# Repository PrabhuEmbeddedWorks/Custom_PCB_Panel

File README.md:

# Custom_PCB_Panel
Tools-KiCad

Designed a custom KiCad symbol and footprint for the DigiSpark PCB, ensuring accurate pin mappings, electrical properties, and mechanical details. The symbol was created with proper pin labeling, while the footprint included precise pad placements, silkscreen, and courtyard outlines for proper component placement and assembly. Both were saved and integrated into the schematic and layout for the DigiSpark project.

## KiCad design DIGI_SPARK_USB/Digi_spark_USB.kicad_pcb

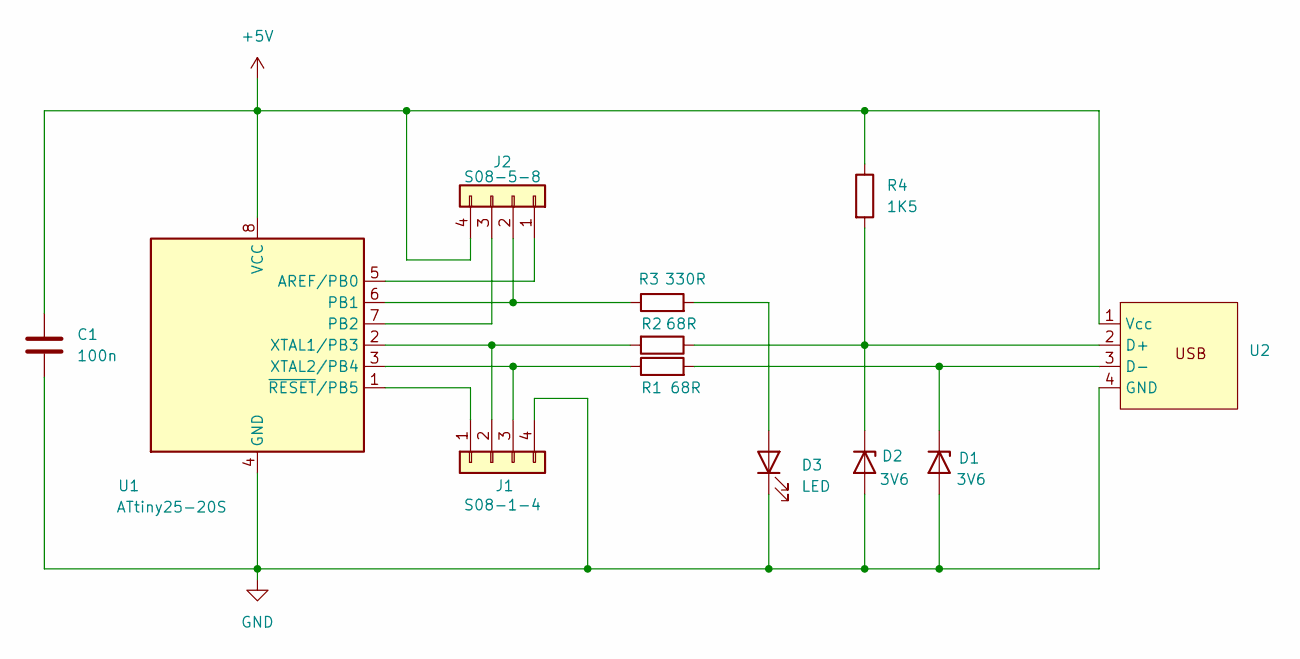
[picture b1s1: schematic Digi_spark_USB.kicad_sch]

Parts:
C1: 100n; C_1206_3216Metric_Pad1.33x1.80mm_HandSolder
D1, D2: 3V6; D_SOD-123
D3: LED; LED_Oval_W5.2mm_H3.8mm
J1: S08-1-4; SolderWire-0.5sqmm_1x04_P4.6mm_D0.9mm_OD2.1mm
J2: S08-5-8; SolderWire-0.5sqmm_1x04_P4.6mm_D0.9mm_OD2.1mm
R1, R2: 68R; R_0805_2012Metric_Pad1.20x1.40mm_HandSolder
R3: 330R; R_0805_2012Metric_Pad1.20x1.40mm_HandSolder
R4: 1K5; R_0805_2012Metric_Pad1.20x1.40mm_HandSolder
U1: ATtiny25-20S; SOIC-8W_5.3x5.3mm_P1.27mm
U2: PCB_USB_connector

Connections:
+5V: C1.1, J2.4, R4.1, U1.8 (VCC), U2.1 (GND)
GND: C1.2, D1.2 (A), D2.2 (A), D3.1 (K), J1.4, U1.4 (GND), U2.4 (Vcc)
unnamed: D1.1 (K), R1.2, U2.3 (D+)
unnamed: D2.1 (K), R2.1, R4.2, U2.2 (D-)
unnamed: D3.2 (A), R3.2
unnamed: J1.1, U1.1 (~RESET/PB5)
unnamed: J1.2, R2.2, U1.2 (XTAL1/PB3)
unnamed: J1.3, R1.1, U1.3 (XTAL2/PB4)
unnamed: J2.1, U1.5 (AREF/PB0)
unnamed: J2.2, R3.1, U1.6 (PB1)
unnamed: J2.3, U1.7 (PB2)

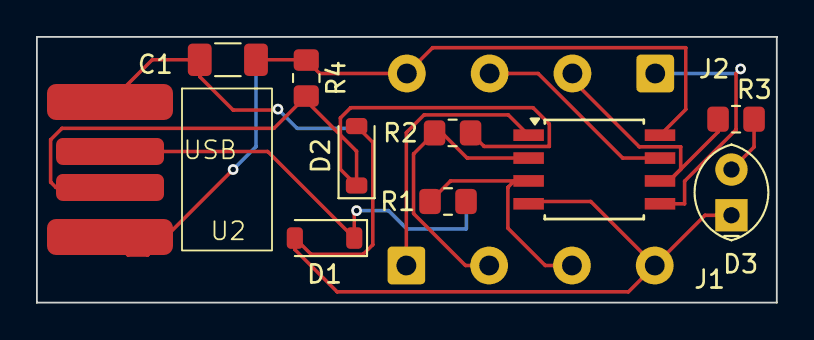
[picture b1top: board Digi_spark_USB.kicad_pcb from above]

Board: 2 copper layers, 41.1 x 14.8 mm, 12 parts (0 on the bottom side), 11 nets.
